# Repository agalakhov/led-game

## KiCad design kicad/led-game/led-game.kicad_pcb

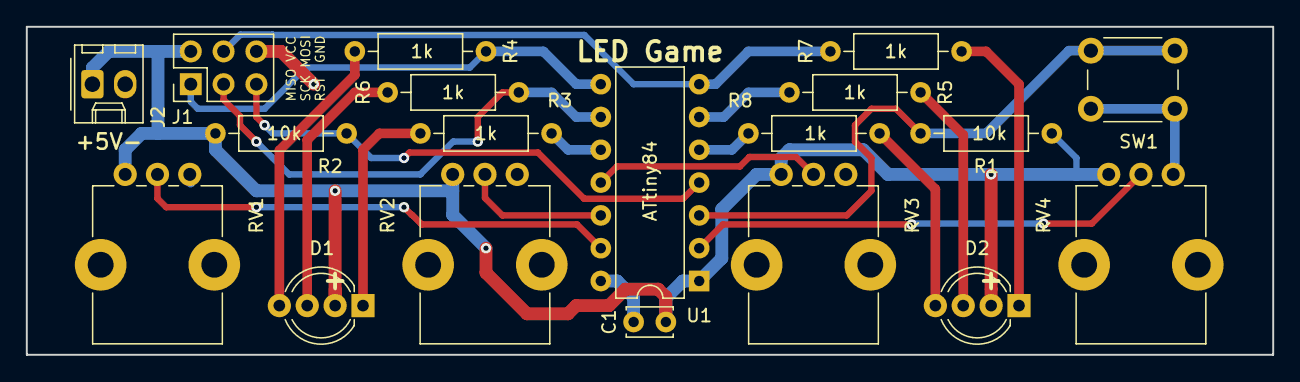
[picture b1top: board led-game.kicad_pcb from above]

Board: 2 copper layers, 96.5 x 25.4 mm, 19 parts (0 on the bottom side), 20 nets.

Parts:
C1: 0.1µ; C_Disc_D3.4mm_W2.1mm_P2.50mm
D1, D2: LED_RAGB; LED_D5.0mm-4_RGB_Wide_Pins
J1: PROG; PinHeader_2x03_P2.54mm_Vertical
J2: POWER; Molex_KK-254_AE-6410-02A_1x02_P2.54mm_Vertical
R1, R2: 10k; R_Axial_DIN0207_L6.3mm_D2.5mm_P10.16mm_Horizontal
R3, R4, R5, R6, R7, R8: 1k; R_Axial_DIN0207_L6.3mm_D2.5mm_P10.16mm_Horizontal
RV1, RV2, RV3, RV4: 50k; Potentiometer_Alps_RK09K_Single_Vertical
SW1: SW_Push; SW_PUSH_6mm_H5mm
U1: ATtiny84; DIP-14_W7.62mm

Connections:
/MISO: J1.1, R4.2, U1.8
/MOSI: J1.4, R7.2, U1.7
/RST: J1.5, R2.2, U1.4
/SCK: J1.3, R6.2, U1.9
GND: C1.1, J1.6, J2.2, RV1.3, RV2.3, RV3.3, RV4.3, SW1.2, U1.14
unnamed: D1.1, R3.1
unnamed: D1.3, R6.1
unnamed: D1.4, R4.1
unnamed: D2.1, R7.1
unnamed: D2.3, R5.1
unnamed: D2.4, R8.1
unnamed: R1.2, SW1.1, U1.3
unnamed: R3.2, U1.10
unnamed: R5.2, U1.6
unnamed: R8.2, U1.5
unnamed: RV1.2, U1.13
unnamed: RV2.2, U1.12
unnamed: RV3.2, U1.11
unnamed: RV4.2, U1.2
VCC: C1.2, D1.2, D2.2, J1.2, J2.1, R1.1, R2.1, RV1.1, RV2.1, RV3.1, RV4.1, U1.1

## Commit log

2019-01-16 Import KiCAD schematics, board and Arduino sketch.
2019-01-16 Typo fix in pin naming.
